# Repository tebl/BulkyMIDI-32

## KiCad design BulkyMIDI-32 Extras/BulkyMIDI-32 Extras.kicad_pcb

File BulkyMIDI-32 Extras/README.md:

# BulkyMIDI-32 Extras
Building the BulkyMIDI-32, I quickly ran into a bit of a problem with the format I had decided upon - I simply desired too many features to be able to fit all of it onto a $5 PCB (100x100mm). The solution came to me, weak and weary in a midnight dreary. Pondering over a quaint volume of forgotten TTL-lore, suddenly a raven came to be sitting upon my chamber door shouting: 

> Take all of the functionality that can be considered *"extra"* somewhere else. This way noone will have to build all of it in order to enjoy having an MT32-PI. 

You don't mess around with ravens, so I did as was told. This is why the project now has an *extras*-board. Build what you need, if you must. It's not like this story was true - except for the part where I ran out of board space.

The additional features provided by this module are as follows:
* RS-232 circuitry for communicating with a PC, this allows the installed Arduino Pro Micro to perform baud rate translation when communicating with MIDI-equipment through a PCs serial port. This is needed because MIDI uses a custom baud rate, generally well outside the tolerances of what a regular serial card can communicate at.
* Passive two-channel audio mixer, allowing you to mix the soundeffects coming from the sound card with that of the MIDI module without dealing with configuring a mixer in software on the card.
* Status LEDs
* Three extra MIDI ports that can individually be configured to serve as additional OUT or THRU ports.

For the most part you would only install the components for the features that you need or want, the links below will allow you to jump to a specific point in the build process and to access other details. Do however start at the beginning, but do not be alarmed at the sheer length of the build process - most of it'll take a lot longer to describe than it is to simply implement them.

- [1> Building the device](#1-building-the-device)
  - [1.1> Soldering it together](#11-soldering-it-together)
  - [1.2> Install LEDs](#12-install-leds)
  - [1.3> Electrolytics](#13-electrolytics)
  - [1.4> Connectors](#14-connectors)
  - [1.5> Installing the firmware](#15-installing-the-firmware)
  - [1.6> Finishing touches](#16-finishing-touches)
- [2> Schematic](#2-schematic)
- [3> BOM](#3-bom)

# 1> Building the device
Building a device such as this assumes you have at least minor experience soldering things together, recommended is that you at the very least have access to a soldering station with adjustable temperature. If currently available, you should probably start with 60/40 rosin core solder as the lead-free alternatives tends to be a bit harder to work with.

With the equipment sorted, now comes the shopping - so head on over to the [BOM](#3-bom)-section for some information on what kind of components that you'll need. Note that with sites such as ebay, AliExpress and similar sites that sell cheap chinese components, you'll need to treat these as a suggested search term and look for something that matches the gallery pictures.

Given the features listed at the start of this document, there are quite possibly a few of those you won't need or want as they can be considered separate from the main device though they will for the most part be related to the rabbit-hole I fell into when first starting out constructing the BulkyMIDI-32. There may certainly be some overlap between them, but it is a starting point (U1 will be needed for both MCU and the main device ports). The colours are as follows:

* **Green** components are used when we want the device to perform baud rate translation, this is used when receiving data via either the RS232-module or MIDI IN that is sent in a different baud rate from what a real MIDI-module expects. The closest baud rate on a PC would be 38400, well outside the tolerance of MIDI devices expecting 31250 baud.
* **Gray** components are only needed when using the *extras* board by itself, this is only relevant for the baud rate translation features described above.
* Components marked in **purple** indicate components directly adding features to the main BulkyMIDI-32 module. These include the addition of a rotary encoder module, additional *MIDI OUT* ports as well as *MIDI THRU* ports.
* **Yellow** components are for the RS-232, the Arduino Pro Micro takes care of handling the baud rate translation between RS-232 and the MIDI ports. 
* Finally, the **blue** components implement a simple passive audio mixer. It supports two channels when the *extras* board is used a standalone module, when connecting to it to the main module the audio output from that is used a third channel.

The build instructions from this point on will aim for the installation of most of the features, but feel free to leave out functionality you don't need according to colour chart above.

**NB!** Don't worry if the sheer length of this document looks intimidating, it's just a running commentary on everything that is done and updated pictures as we go along in the build process. Everything will be explained in due time, quite possibly including a lot more information than what would normally be needed for anyone with passable familiarity with soldering things together.

## 1.1> Soldering it together
The construction of this unit should be fairly straight-forward, just take your time in order to make sure everything goes into place - more or less straight. I usually recommend starting by having a good look at the PCBs, then try to figure out where the components should go and in particular the orientation they should be installed - it may be a case of round thing going into another round thing, but this is electronics and the small details matter. As mentioned in the previous section, you may not want every feature so pay attention to the colour coding when deciding what to leave out.

**NB!** This is revision F of the board, the changes to the revision G is the addition of a couple of diodes. 

I will usually try to install components sorted by their physical size, doing it this way means you'll have an easier time keeping everything from looking somewhat crooked. This is your board, your build and you want it perfect - don't you? If you said no, then go sit in the corner because I worked hard on creating this for myself and whoever wants to build one.

Here we've started by soldering all of the resistors, ensuring that we're using the correct values in each position. A single glass 1n4148 diode has also been installed, pay particular attention so that the black band matches that of the markings on the PCB. As previously mentioned, revision G also includes a 1n4001 diode to be installed at D1 (to the right of the *BAUD RATE*-diagram) - this is a larger black diode with a silver band instead and should also be installed as indicated.

Given that space will inevitably get tight, I like to get the solder jumpers handled early - less chance of accidentally melting a socket or two.
- You **need** to make a choice for **JP1-JP3**, regardless of whether you'll be installing the additional MIDI-connectors to the board - soldered across pins *1-2* makes the connector a THRU port while *2-3* makes it an extra OUT port. The little triangle above one of the pads denotes the first pin.
- The same goes for the **NO_555** jumper, soldering pins *1-2* when you're installing all of the LED components including the *555* and so on. Solder across pins *2-3* when building a simpler version of the board.

Sockets should be installed for the three ICs needed for the complete unit - you could probably manage without them if you know that you'll only be using known good parts. However, they're cheap and you could probably afford to not be quite so *cheap* as to skip them! Match the indent on the socket with that on the PCB. I recommend tacking opposing corners into place, then reheat the pins and push the socket flush against the board before soldering the remaining pins.

We've also gone ahead and installed our non-polarized capacitors, for the most part these will simply be 100nF (component marked *104*) decoupling caps added to ensure that the ICs function as intended and no values will be printed for them on the PCB. One of them will however not be the same as the rest, it is a 10nF capacitor that can be found directly below the space marked *74HCT14* (the component itself will be marked with the code *103*).

A single transistor is also used, a 2n3906 in a TO-92 package. If you're lucky enough to find them at a reasonable price, you can get transistors with pre-bent legs to match the footprint directly - because I couldn't, I instead just bent them outwards myself. The reason for this is simply that I prefer soldering with a larger tip, so the use of a wider footprint makes it a lot easier to avoid accidentally shorting the legs together. Looking at one from the top, you'll notice that it has a flat and a curved side to them - this needs to be matched up to the footprint.

## 1.2> Install LEDs
Somehow I managed the rather impressive task of coming up with a rather strange way of mounting the LEDs, requiring me to write a separate chapter on the things. Anyway, the idea was to have the LEDs facing forwards with the leads having been bent so that the rear of the LED sit flush against the edge of the PCB.

Each of the pins on the LED have their own names, it's actually just a diode that happens to light up when energized. I can never remember which of them is which, so for ease of reference I'll just say that you need to ensure that the longer pin goes into the round pad. If you look closely at the LED you'll see that the legs have a bit of a flattened bit to it, this is the part that needs to be in the PCB when bending then push the plastic of the housing flat against the PCB edge.

Solder in place once you are happy with the results. Personally I don't like the light bleed you get between the LEDs, generally they are so efficient that they'll appear to light up slightly just from the glow of the LED beside it. One way to reduce that is to slide a section on top of the LED so that only the front part of it is uncovered.

## 1.3> Electrolytics
With the LEDs in place, we've already moved on to other things. The electrolytic capacitors, or condensers if you're getting old like me. The one at *C6* ensures that everything on the board is properly powered. It's polarized component, meaning that we need to put it in the correct way or it won't work right. The stripe on its housing indicates the negative side, this matches up with the filled-in area of the footprint. As with the LEDs, the pins certainly have names that I'm incapable of remembering, so I'll just tell you to put the longer pin into the hole closest to the little plus sign (might need a magnifier to find it).

The same goes for *C8*, it is a smaller capacitor used for the timing on the 555. If you like to see the little LED flickering to show activity, just go ahead and install the 1uF component as indicated. If you would like it to stay on as long as there's data coming in at a regular pace, consider increasing the value to 3.3uF or even 4.7uF instead.

## 1.4> Connectors

Finally getting around to something intended for a bit of audio, the 3.5mm audio jacks. Given that the board incorporates a way of passively mixing up to two signals into the main audio coming from the MT32-PI, we probably should use differently coloured connectors to separate the output (green) from the inputs (black connectors). Technically the inputs should have been blue or quite possibly red, but I can't seem to find someone selling them, so I went with black instead. 

One step we need to pay particular attention to is how the *extras*-board would connect up with the main *BulkyMIDI-32*, specified as *J4* here. For my prototypes I've installed some extra long female pin headers as the one shown above on the main unit, only requiring standard male pin headers on this board. The spacing between these need to be correct, so I recommend that you try out the fit between the two modules with 20mm hex standoffs in between - **before** actually soldering anything in place.

If you've decided upon how to connect the *extras*-board to the main board, then we'll continue on with the installation - starting with making a few decisions on how to install the Arduino Pro Micro.

I need to say a few words about the various Arduino Pro Micro variants that are out there, one of the common variants encountered is more narrow than the others - to accommodate for this there is a duplicated row on one side. For reference I'm installing some female pin headers onto the Arduino itself, that way I can remove the board and use it for something else later. If you don't want to do all that you could just solder the two together, just make sure to install them according to the width of the board that you have.

The rest is to install the rest. Merely this and nothing more.

That includes a female right-angle DB9 connector, a barrel connector and at least the MIDI OUT on the top right of the board. If you want to use the audio mixer you'll need the potentiomenters as well.

The added MIDI ports on the right side of the module, labelled MIDI 1 through 3, can be set to either be used as *MIDI THRU* or *MIDI OUT*. From the best of my knowledge, the *THRU* variety is used by the MT32-PI to send a copy of all received MIDI messages to any connected devices. *OUT* on the other hand will be messages sent by MT32-PI, often a copy of the same messages though they may have had changes and filtering applied to them. *JP1* through *JP3* specifies the configuration for each connection, just pay attention that the order of them may not be as expected.

**NB!** If you have not already done as told, you need to solder each of these solder jumpers - even if you're skipping the installation of the connectors. When in doubt or for where you don't want to make an informed decision, just link pins 1-2 with the little triangle indicating pin 1.

## 1.5> Installing the firmware
This section will be a bit truncated, simply because the project includes different firmware that can be installed on the Arduino Pro Micro, each bringing different functionality into the mix. When in doubt the firmware you're looking for is probably the BaudRateConverter.

- [BaudRateConverter](https://github.com/tebl/BulkyMIDI-32/tree/main/software/arduino/BaudrateConverter) takes care of reading MIDI-data sent to it over RS-232, then retransmitting it over a standard 5-pin MIDI-cable. This is handy when using the device with an old laptop that may not have a MIDI-enabled gameport, but instead has a free serial port.
- [DebugMIDI](https://github.com/tebl/BulkyMIDI-32/tree/main/software/arduino/DebugMidi) gives you a simple debugging tool for MIDI-data, printing details for MIDI-messages received via a MIDI-cable. This is all handled via a command-line interface available via USB (running at 115200 baud).

Most of these will in some part need the [Arduino MIDI Library](https://github.com/FortySevenEffects/arduino_midi_library), the installation of which will be somewhat different depending on your choice of IDE for Arduino. PlatformIO, the one I'm using has the capability of installing the libraries for you automatically, but as as the Arduino IDE remains the most used I'll cover the process going forward.

Installing additional libraries in the Arduino IDE is done from *Tools* -> *Manage libraries*, the resulting dialog allows you to search for them by name. Unfortunately the search function leaves quite a bit to be desired and there are quite a lot of them to choose from, so I recommend limiting by the topic *Communication* before attempting to browse the results. The one you're looking for is *MIDI Library* by Francois Best. Click install to have the software do its thing. 

The second issue is simply that the *Arduino Pro Micro* isn't actually an official board created by Arduino, it's a significantly smaller Chinese copy of the Arduino Leonardo. What that means for us is that it doesn't have a suitable board definition for this board out of the box. This is easily fixed, going from *Tools* -> *Board: ...* .> *Boards Manager ...* - the one to look for will be named *SparkFun AVR Boards*.

The next step is simply to select the board type as *SparkFun Pro Micro*, under *Processor* you need to ensure that *ATMega32U4 (5v, 16Mhz)* have been selected. Attempting to upload code to the board with the wrong setting here may cause problems communicating with it later, it's recoverrable - it's just an annoying process that involves shorting the reset pin at a specific point on startup.

With everything set up correctly, simply hit compile and upload to send it over to the Arduino Pro Micro. This should complete without any errors.

## 1.6> Finishing touches
With the firmware in place, there isn't much more that is left to do other than connect the two modules together using the 20mm standoffs in between the two, making sure that the central connector mates up correctly. Add the faceplate to the top, finally a front plate goes on the front of the device. If you have any knobs that will fit onto the knurled shafts of the potentiometers, those also go a long way towards a professional look. You may find that some of the rotary encoders come with a D-type shaft instead, but it may be worth ordering one with the same shaft as the potentiometers - makes it a lot easier to find matching knobs.

With all of that done, it's time to enjoy some game - or at the very least have it loop the games title music, just to listen to all the glory that is the Roland MT-32 (at least as close as we can get without buying one). 

# 2> Schematic
The supplied KiCad files should be sufficient as both a schematic and as a  starting point for ordering PCBs (basically you could just zip the contents of the export folder and upload that on a fabrication site), the schematic is also available in [PDF-format](https://github.com/tebl/BulkyMIDI-32/tree/main/documentation/schematic) and this is what you'll need to print and work your way through this things don't work as expected after assembly.

# 3> BOM
Most parts should be easy to get a hold of from your favourite local electronic component shop, but given that I don't have access to such shops where I live so everything was based on whatever I could get cheapest from eBay/AliExpress. You can often get free shipping, but plan on waiting 3-4 weeks for delivery so plan accordingly.

As detailed elsewhere in the [build](#1-building-the-device) portion of this document, you can simply choose to install the features you want in order to cut down on the construction costs or simply limit yourself to those that you have the parts for. To keep the BOM-portion below somewhat readable, the item counts in parenthesis are optional and consists mainly of parts related to the baud rate conversion feature as well as additional *MIDI OUT* and *MIDI THRU* ports. Note that some of the listings have been repeated as they are listed with different description, so order what you need and check the list twice.

| Reference               | Item                                                              | Count | Order  |
| ----------------------- | ----------------------------------------------------------------- | ----- | ------ |
| BulkyMIDI-32 Extras     | Fabricate using Gerber files                                      |     1 | [PCBWay](https://www.pcbway.com/project/shareproject/BulkyMIDI_32_Extras_9be44f98.html)
| A1                      | Arduino Pro Micro (5v 16Mhz)                                      |    (1)|
|                         | 12-pin straight pin header                                        |    (2)|
| C1,C10                  | 100nF ceramic capacitor (5mm)                                     |     2 |
| C2-C5,C11 *             | 100nF ceramic capacitor (5mm)                                     |     5 |
| C6                      | 470uF electrolytic capacitor (8mm x 3.5mm)                        |     1 |
| C8                      | 1uF electrolytic capacitor (5mm x 2mm)                            |     1 |
| C9                      | 10nF ceramic capacitor (5mm)                                      |     1 |
| D2,D4                   | 5mm LEDs, preferably frosted (not the bright clear ones)          |    (3)|
| D1,D5                   | 1N4001 diode DO-41                                                |     2 |
| D3 *                    | 1N4148N small signal diode (DO-35)                                |    (1)|
| J1                      | 2.1mm x 5.5mm barrel plug                                         |    (1)|
| J4                      | 10-pin dual row female pin header (extra long, see [documentation](#14-connectors)) |     1 |
| J2,J3,J5,J10,J11        | Female S-terminal 5pin DIN PCB                                    |    (5)|
| J6 *                    | Right-angle female DB9 connector (PCB mount)                      |    (1)|
| J7-J9                   | PJ-317 (5-pin 3.5mm audio jack), preferably 2x blue and 1x green  |     3 |
| J12 *                   | 6-pin segment of male pin headers, with pin 5 removed             |    (1)|
| J14 *                   | 2-pin segment of male pin headers                                 |    (1)|
| J13 *                   | 2x3 segment of dual row male pin headers                          |    (1)|
| J14 *                   | 2x2 segment of dual row male pin headers                          |    (1)|
| J16                     | RS-232-module stacked on top of J6, wired to pads below module    |    (1)|
| JP7                     | 2-pin segment of male pin headers                                 |     1 |
| Q1                      | 2n3906 transistor (TO-92)                                         |     1 |
| R1,R2,R18 *             | 220 ohm resistor                                                  |    (3)|
| R3,R6,R13,R14,R15,R16 * | 220 ohm resistor                                                  |    (6)|
| R5                      | 2k2 (2200) ohm resistor                                           |    (1)|
| R7-R12                  | 1k ohm resistor                                                   |     6 |
| R17 *                   | 10k ohm resistor                                                  |    (1)|
| R19                     | 2k2 (2200) ohm resistor                                           |     2 |
| R20 *                   | 2k2 (2200) ohm resistor                                           |    (1)|
| R21                     | 100k ohm resistor                                                 |     1 |
| R22                     | 10k ohm resistor                                                  |     1 |
| RV1,RV2                 | RV097G 10k (stereo audio potentimeter)                            |     2 |
| U1                      | 74HCT14 (DIP-14)                                                  |     1 |
| U2 **                   | MAX232A (DIP-16)                                                  |    (1)|
| U3 *                    | 6N138 opto-coupler (DIP-8)                                        |    (1)|
| U4                      | NE555P (DIP-8)                                                    |     1 |
| Mounting ****           | Nylon M3 hex standoffs 20mm (M-F)                                 |     4 |
| Mounting ****           | Nylon M3x6mm nylon nuts                                           |     6 |

*) These components are only needed when installing the MCU for baud rate conversion.

**) Note the specification of a MAX232**A**, the older MAX232 without the *A* won't function without changes to the circuit. The same goes for Chinese clones, often sold as MAX232CPE. When in doubt, pick these up from a reputable electronics vendor.

***) These are used to hold the RS-232-modules in place, especially if you plan on installing two of them. With only the one module you can use shorter screws instead.

****) These are used in various places of the project, these are available in the form of kits usually advertised *M3 nylon standoff kit* which should contain most of what you'd need.

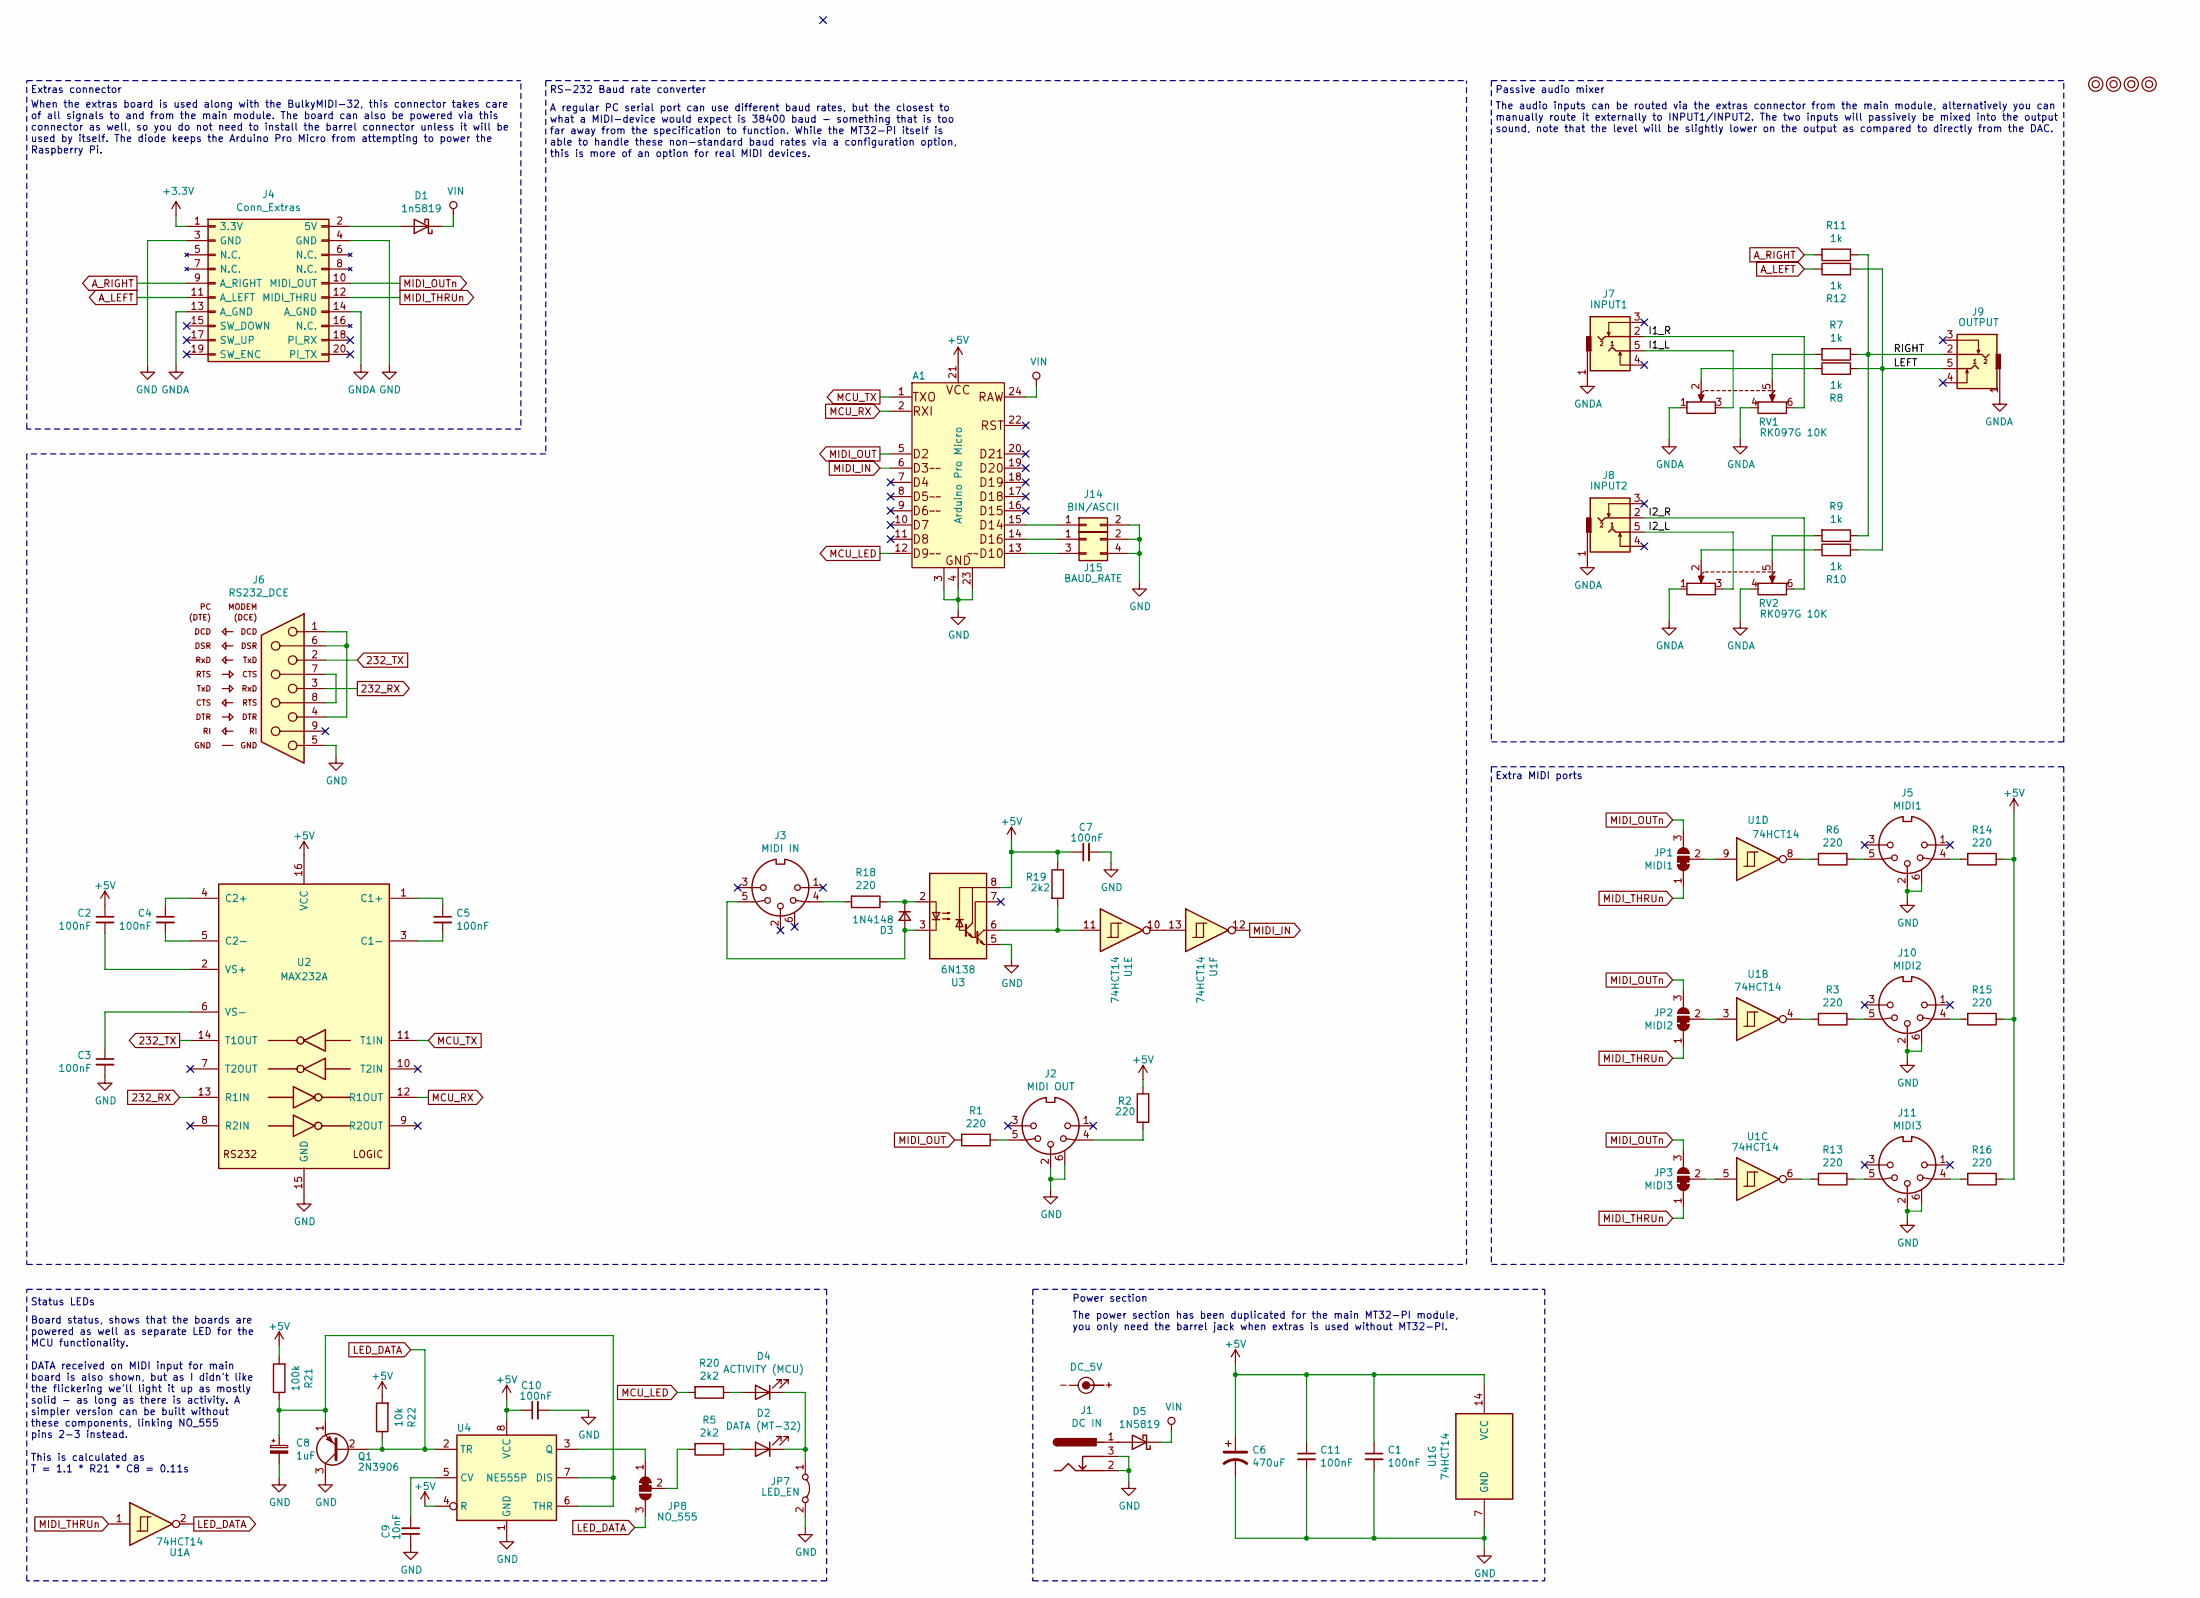
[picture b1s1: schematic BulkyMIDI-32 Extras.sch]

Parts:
A1: Arduino Pro Micro; Arduino_Pro_Micro
C1, C2, C3, C4, C5, C7, C10, C11: 100nF; C_Disc_D4.7mm_W2.5mm_P5.00mm
C6: 470uF; CP_Radial_D8.0mm_P3.50mm
C8: 1uF; CP_Radial_D5.0mm_P2.00mm
C9: 10nF; C_Disc_D4.7mm_W2.5mm_P5.00mm
D1: 1n5819; D_DO-41_SOD81_P10.16mm_Horizontal
D2: DATA (MT-32); LED_D5.0mm_Horizontal_O1.27mm_Z3.0mm
D3: 1N4148; D_DO-35_SOD27_P7.62mm_Horizontal
D4: ACTIVITY (MCU); LED_D5.0mm_Horizontal_O1.27mm_Z3.0mm
D5: 1N5819; D_DO-41_SOD81_P10.16mm_Horizontal
J1: DC IN; BARREL_JACK
J2: MIDI OUT; DIN5_MIDI_OUT
J3: MIDI IN; DIN5_MIDI_IN
J4: Conn_Extras; PinHeader_2x10_P2.54mm_Vertical
J5: MIDI1; DIN5_MIDI_OUT
J6: RS232_DCE; DSUB-9_Female_Horizontal_P2.77x2.84mm_EdgePinOffset7.70mm_H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
J7: INPUT1; PJ-317_IN
J8: INPUT2; PJ-317_IN
J9: OUTPUT; PJ-317_OUT
J10: MIDI2; DIN5_MIDI_OUT
J11: MIDI3; DIN5_MIDI_OUT
J14: BIN/ASCII; PinHeader_1x02_P2.54mm_Vertical
J15: BAUD_RATE; PinHeader_2x02_P2.54mm_Vertical
JP1: MIDI1; SolderJumper-3_P1.3mm_Open_Pad1.0x1.5mm
JP2: MIDI2; SolderJumper-3_P1.3mm_Open_Pad1.0x1.5mm
JP3: MIDI3; SolderJumper-3_P1.3mm_Open_Pad1.0x1.5mm
JP7: LED_EN; PinHeader_1x02_P2.54mm_Vertical
JP8: NO_555; SolderJumper-3_P1.3mm_Open_Pad1.0x1.5mm
M1, M2, M3, M4: Mounting; M3
Q1: 2N3906; TO-92_Inline_Wide
R1, R2, R3, R6, R13, R14, R15, R16, R18: 220; R_Axial_DIN0207_L6.3mm_D2.5mm_P10.16mm_Horizontal
R5, R19, R20: 2k2; R_Axial_DIN0207_L6.3mm_D2.5mm_P10.16mm_Horizontal
R7, R8, R9, R10, R11, R12: 1k; R_Axial_DIN0207_L6.3mm_D2.5mm_P10.16mm_Horizontal
R21: 100k; R_Axial_DIN0207_L6.3mm_D2.5mm_P10.16mm_Horizontal
R22: 10k; R_Axial_DIN0207_L6.3mm_D2.5mm_P10.16mm_Horizontal
RV1, RV2: RK097G 10K; RK097G
SYM1: DC_5V; PWR_Specification
U1: 74HCT14; DIP-14_W7.62mm_Socket_LongPads
U2: MAX232A; DIP-16_W7.62mm_Socket_LongPads
U3: 6N138; DIP-8_W7.62mm_Socket_LongPads
U4: NE555P; DIP-8_W7.62mm_Socket_LongPads

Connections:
232_RX: J6.3, U2.13 (R1IN)
232_TX: J6.2, U2.14 (T1OUT)
+5V: A1.21 (VCC), C1.1, C2.1, C6.1, C7.1, C10.1, C11.1, R2.1, R14.1, R15.1, R16.1, R19.1, R21.2, R22.2, U1.14 (VCC), U2.16 (VCC), U3.8 (VCC), U4.4 (R), U4.8 (VCC)
/I1_L: J7.5, RV1.3
/I1_R: J7.2, RV1.6
/I2_L: J8.5, RV2.3
/I2_R: J8.2, RV2.6
/LEFT: J9.5, R8.2, R10.2, R12.2
/RIGHT: J9.2, R7.1, R9.1, R11.1
A_LEFT: J4.11 (A_LEFT), R12.1
A_RIGHT: J4.9 (A_RIGHT), R11.2
GND: A1.3 (GND), A1.4 (GND), A1.23 (GND), C1.2, C3.2, C6.2, C7.2, C8.2, C9.1, C10.2, C11.2, J1.2, J1.3, J2.2, J2.6, J4.3 (GND), J4.4 (GND), J5.2, J5.6, J6.5, J10.2, J10.6, J11.2, J11.6, J14.2, J15.2, J15.4, JP7.2 (B), Q1.3 (C), U1.7 (GND), U2.15 (GND), U3.5 (GND), U4.1 (GND)
GNDA: J4.13 (A_GND), J4.14 (A_GND), J7.1, J8.1, J9.1, RV1.1, RV1.4, RV2.1, RV2.4
LED_DATA: JP8.3 (B), Q1.2 (B), R22.1, U1.2, U4.2 (TR)
MCU_LED: A1.12 (D9), R20.2
MCU_RX: A1.2 (RXI), U2.12 (R1OUT)
MCU_TX: A1.1 (TXO), U2.11 (T1IN)
MIDI_IN: A1.6 (D3), U1.12
MIDI_OUT: A1.5 (D2), R1.2
MIDI_OUTn: J4.10 (MIDI_OUT), JP1.3 (B), JP2.3 (B), JP3.3 (B)
MIDI_THRUn: J4.12 (MIDI_THRU), JP1.1 (A), JP2.1 (A), JP3.1 (A), U1.1
unnamed: A1.13 (D10), J15.3
unnamed: A1.14 (D16), J15.1
unnamed: A1.15 (D14), J14.1
unnamed: C2.2, U2.2 (VS+)
unnamed: C3.1, U2.6 (VS-)
unnamed: C4.1, U2.4 (C2+)
unnamed: C4.2, U2.5 (C2-)
unnamed: C5.1, U2.1 (C1+)
unnamed: C5.2, U2.3 (C1-)
unnamed: C8.1, Q1.1 (E), R21.1, U4.6 (THR), U4.7 (DIS)
unnamed: C9.2, U4.5 (CV)
unnamed: D1.2 (A), J4.2 (5V)
unnamed: D2.1 (K), D4.1 (K), JP7.1 (A)
unnamed: D2.2 (A), R5.1
unnamed: D3.1 (K), R18.1, U3.2 (C1)
unnamed: D3.2 (A), J3.5, U3.3 (C2)
unnamed: D4.2 (A), R20.1
unnamed: D5.2 (A), J1.1
unnamed: J2.4, R2.2
unnamed: J2.5, R1.1
unnamed: J3.4, R18.2
unnamed: J5.4, R14.2
unnamed: J5.5, R6.1
unnamed: J6.1, J6.4, J6.6
unnamed: J6.7, J6.8
unnamed: J10.4, R15.2
unnamed: J10.5, R3.1
unnamed: J11.4, R16.2
unnamed: J11.5, R13.1
unnamed: JP1.2 (C), U1.9
unnamed: JP2.2 (C), U1.3
unnamed: JP3.2 (C), U1.5
unnamed: JP8.1 (A), U4.3 (Q)
unnamed: JP8.2 (C), R5.2
unnamed: R3.2, U1.4
unnamed: R6.2, U1.8
unnamed: R7.2, RV1.5
unnamed: R8.1, RV1.2
unnamed: R9.2, RV2.5
unnamed: R10.1, RV2.2
unnamed: R13.2, U1.6
unnamed: R19.2, U1.11, U3.6 (VO2)
unnamed: U1.10, U1.13
VIN: A1.24 (RAW), D1.1 (K), D5.1 (K)

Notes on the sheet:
RS-232 Baud rate converter
Power section
Passive audio mixer
Extras connector
When the extras board is used along with the BulkyMIDI-32, this connector takes care of all signals to and from the main module. The board can also be powered via this connector as well, so you do not need to install the barrel connector unless it will be used by itself. The diode keeps the Arduino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
The audio inputs can be routed via the extras connector from the main module, alternatively you can manually route it externally to INPUT1/INPUT2. The two inputs will passively be mixed into the output sound, note that the level will be slightly lower on the output as compared to directly from the 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
Status LEDs
Extra MIDI ports
Board status, shows that the boards are powered as well as separate LED for the MCU functionality. DATA received on MIDI input for main board is also shown, but as I didn't like the flickering we'll light it up as mostly solid - as long as there is activity. A simpler version can be built without t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
The power section has been duplicated for the main MT32-PI module, you only need the barrel jack when extras is used without MT32-PI.
A regular PC serial port can use different baud rates, but the closest to what a MIDI-device would expect is 38400 baud - something that is too far away from the specification to function. While the MT32-PI itself is able to handle these non-standard baud rates via a configuration option, this is m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

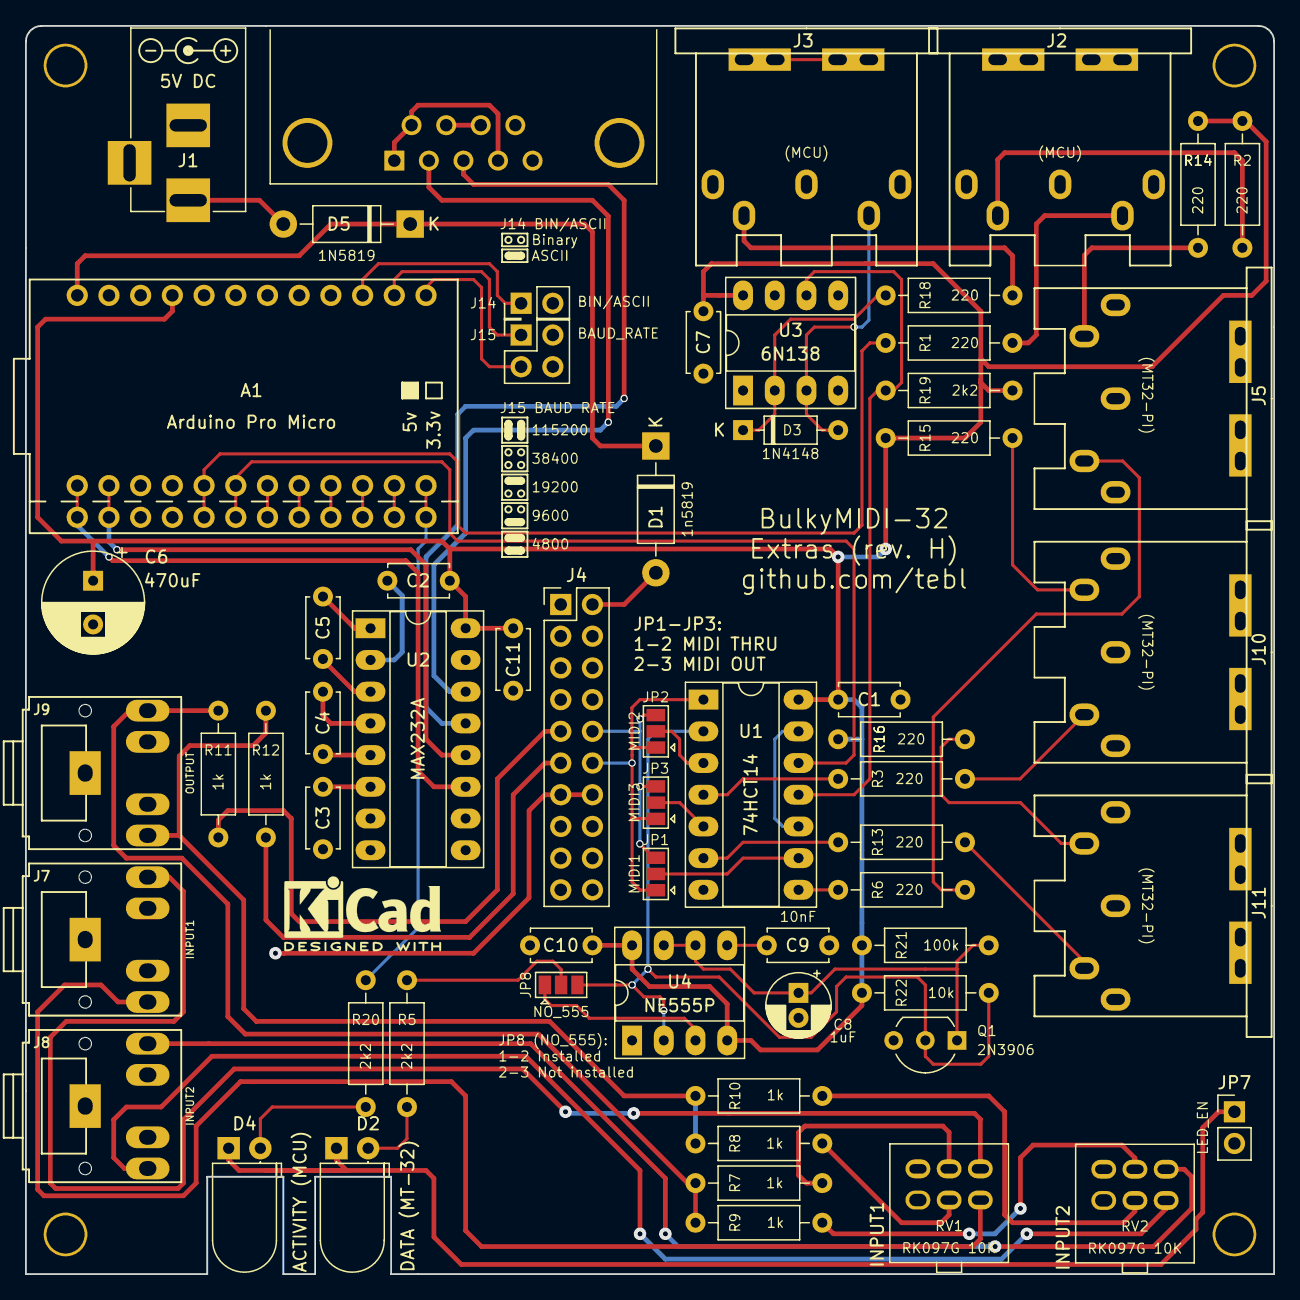
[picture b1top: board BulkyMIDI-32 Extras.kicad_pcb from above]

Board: 2 copper layers, 100.0 x 100.0 mm, 67 parts (0 on the bottom side), 65 nets.

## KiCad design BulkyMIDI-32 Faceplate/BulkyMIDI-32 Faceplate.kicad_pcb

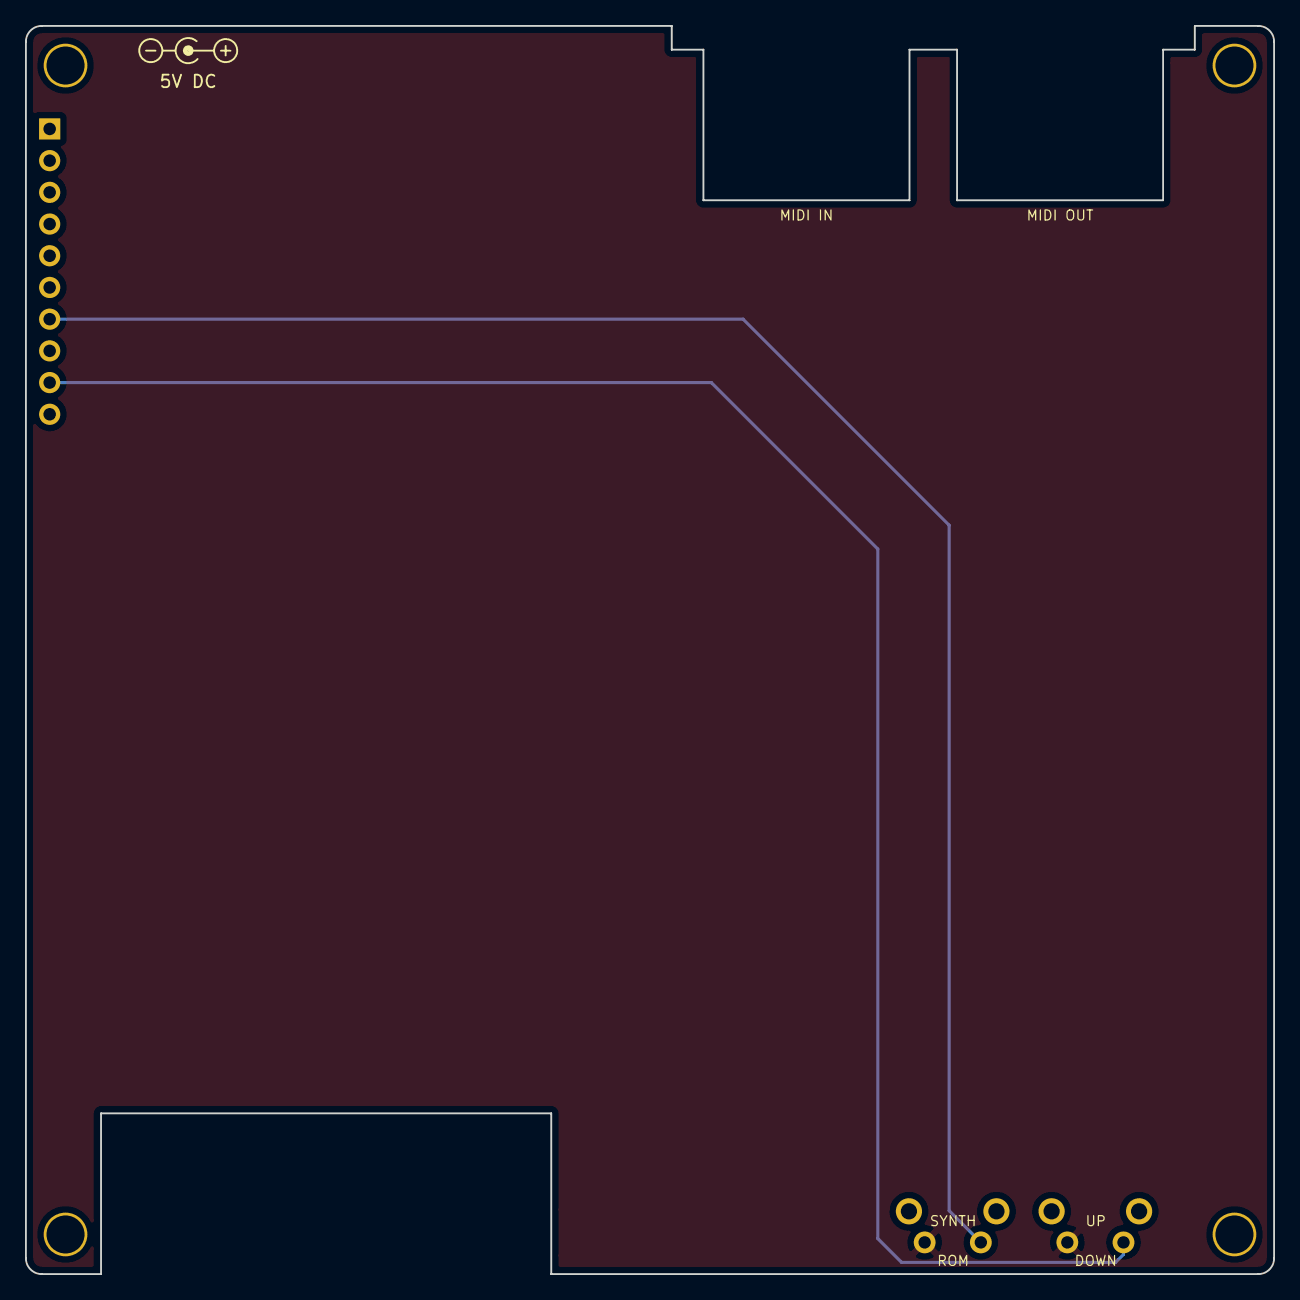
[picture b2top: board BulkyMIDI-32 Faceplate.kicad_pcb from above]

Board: 2 copper layers, 100.0 x 100.0 mm, 7 parts (1 on the bottom side), 3 nets.

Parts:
J4: Faceplate; PinHeader_1x10_P2.54mm_Vertical
M1, M2, M3, M4: Mounting; M3
SW1: SYNTH; SW_Tactile_SPST_Angled_PTS645Vx39-2LFS_Underside
SW4: VOL_UP; SW_Tactile_SPST_Angled_PTS645Vx39-2LFS_Underside

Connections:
GND: SW1.1, SW4.1
SW_SYNTH: J4.7, SW1.2
SW_UP: J4.9, SW4.2

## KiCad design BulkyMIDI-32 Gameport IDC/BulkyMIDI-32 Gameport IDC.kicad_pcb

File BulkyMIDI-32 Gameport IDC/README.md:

# BulkyMIDI-32 Gameport (IDC)
This is an alternative version of [BulkyMIDI-32 Gameport](https://github.com/tebl/BulkyMIDI-32/tree/main/BulkyMIDI-32%20Gameport), the difference is that instead of a right-angle DB15 connector we've got an IDC connector. For more general information about what this adapter is and what it is, check out the documentation for the regular version.

Using a cable increases the cost of the unit slightly, as we'd need to buy the cable including any connectors not already on it (I've seen Uxcell-branded cables that are ready made on AliExpress and Ebay). Having the adapter on a cable means we've got the flexibility of using it mostly everywhere, primarily by not getting in the way of other inputs on the motherboard or sound card. The pinout should also match the same [pinout](https://www.frontx.com/cpx091_2.html) used on motherboard breakout cables (usually with pin 16 missing), so in theory you could use a 2x8 pin ribbon cable and connect it directly to a motherboard with internal gameport connector.

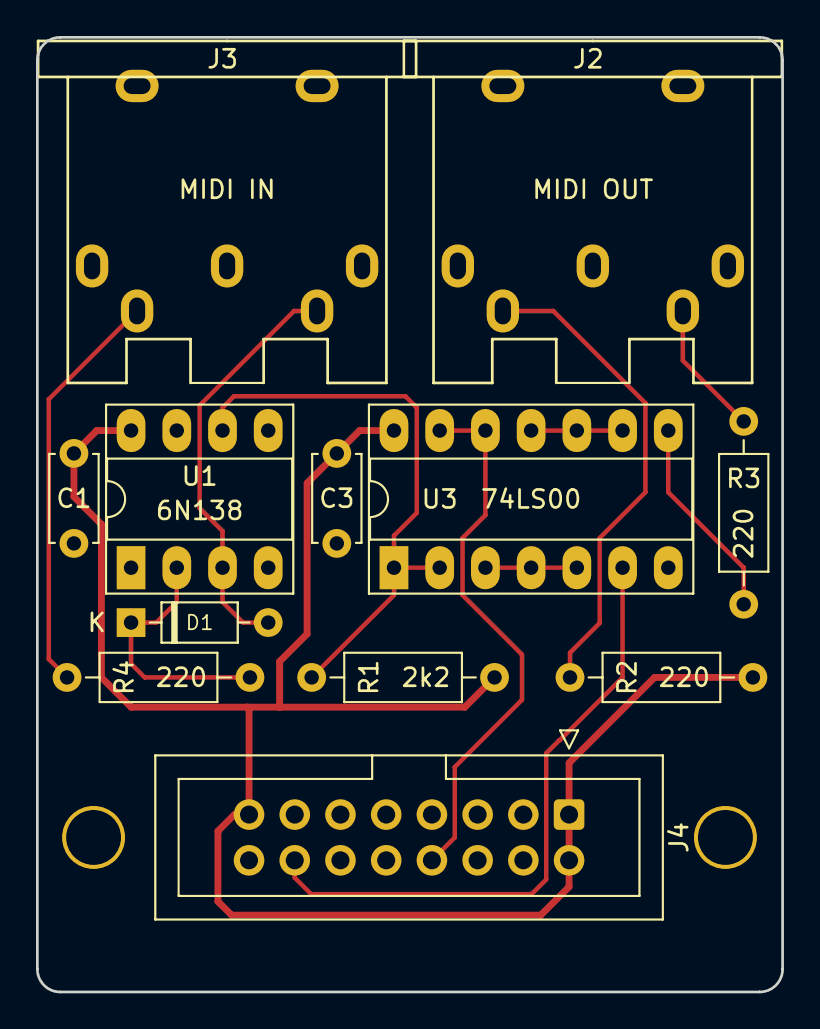
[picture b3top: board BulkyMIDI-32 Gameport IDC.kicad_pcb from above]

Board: 2 copper layers, 41.4 x 53.0 mm, 14 parts (0 on the bottom side), 13 nets.

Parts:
C1, C3: 100nF; C_Disc_D4.7mm_W2.5mm_P5.00mm
D1: 1N4148; D_DO-35_SOD27_P7.62mm_Horizontal
J2: MIDI OUT; DIN5_MIDI
J3: MIDI IN; DIN5_MIDI
J4: Gameport; Gameport_IDC
M1, M2: Mounting; M3
R1: 2k2; R_Axial_DIN0207_L6.3mm_D2.5mm_P10.16mm_Horizontal
R2, R3, R4: 220; R_Axial_DIN0207_L6.3mm_D2.5mm_P10.16mm_Horizontal
U1: 6N138; DIP-8_W7.62mm_Socket_LongPads
U3: 74LS00; DIP-14_W7.62mm_Socket_LongPads

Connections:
+5V: C1.1, C3.1, J4.1, J4.8, J4.9, R1.1, R2.1, U1.8, U3.14
GND: C1.2, C3.2, J2.2, J4.4, J4.5, U1.5, U3.7
MIDI_RxD: J4.15, U3.6
MIDI_TxD: J4.12, U3.12, U3.13
unnamed: D1.1, R4.1, U1.2
unnamed: D1.2, J3.5, U1.3
unnamed: J2.4, R2.2
unnamed: J2.5, R3.1
unnamed: J3.4, R4.2
unnamed: R1.2, U1.6, U3.1, U3.2
unnamed: R3.2, U3.8
unnamed: U3.3, U3.4, U3.5
unnamed: U3.9, U3.10, U3.11

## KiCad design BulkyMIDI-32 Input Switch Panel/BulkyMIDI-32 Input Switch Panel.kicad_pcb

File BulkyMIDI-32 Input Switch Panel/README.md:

# BulkyMIDI-32 Input Switch Panel
This is a front-facing panel for controlling the *BulkyMIDI-32 Input Switch*, while optional by design I find that it makes the system a lot more enjoyable - both when in use, and living in a pile on my desk. The main PCB didn't have suffiecient room for the LEDs either, so if you'd like a little feedback on the currently active input channel then this is where you'd mount those without getting overly creative.

- [1> Building the device](#1-building-the-device)
  - [1.1> Soldering it together](#11-soldering-it-together)
- [2> Schematic](#2-schematic)
- [3> BOM](#3-bom)

# 1> Building the device
Building a device such as this assumes you have at least minor experience soldering things together, recommended is that you at the very least have access to a soldering station with adjustable temperature. If currently available, you should probably start with 60/40 rosin core solder as the lead-free alternatives tends to be a bit harder to work with.

With requirements for basic equipment sorted, we need to talk a bit about what you want to achieve while building this project. The reason I ask is that while you can build a functional [BulkyMIDI-32 Input Switch](https://github.com/tebl/BulkyMIDI-32/tree/main/BulkyMIDI-32%20Input%20Switch) using that module alone, you can also build the complete version of it - this includes including front panels (this module), as well as a set of two faceplates.

Now that you know what you want to build, we can get started on the most expensive step in any build process - shopping! So, head on over to the [BOM](#3-bom)-section for some information on what kind of components that you'll need. While I would have liked to give you specific part numbers for "reputable" electronic part suppliers, I can't afford to shop there so I usually make due with what I can find on sites such as ebay, AliExpress and any similar sites that sell cheap chinese components. The downside to this is that I can't link to a part directly and expect it to stay listed, so you'll need to consider the description listed as suggested search terms.

## 1.1> Soldering it together

The construction of this unit should be fairly straight-forward, just take your time in order to make sure everything goes into place - more or less straight. I usually recommend starting by having a good look at the PCBs, try to figure out where all of the listed components go and in which orientation they go in (all of this should be clearly marked on the silkscreen). 

The first component to be added is the right-angle pin headers, these are soldered on the front side of the board instead of the component side. I've found that these are often somewhat warped, so I usually try to just solder the outer edges first, then reheat and adjust so that the plastic part sits completely flush against the board before tackling the remaining pins.

The next component to go on are the 8mm hex standoffs, they in particular need to be positioned so that a flat edge lines up with the lef and right edges of the PCB. As these are just nylon, I've made things slightly easier for myself by using a sharp knife to trim a bit off the vertical edges of them - in particular the one that sits just above the power LED.

Here I've simply inserted the LEDs into the footprints (longer pin goes into the round pad), the same goes for the six switches before adding the front panel to the front of it.  Continuing on with the LEDs I'll tack one of the pins into place, then while reheating the pin I'll try and push slightly on it to ensure that it is perfectly aligned with the holes on the front panel before soldering the remaining pin. The switches mostly stick to their expected alignment, but feel free to use the same method except that you push from the from.

The front panel have been removed again, mostly because it'll slightly be in the way when installing it onto the main [BulkyMIDI-32 Input Switch](https://github.com/tebl/BulkyMIDI-32/tree/main/BulkyMIDI-32%20Input%20Switch) PCB. If you're a perfectionist like me, you may want to deal with some of the light bleed that you'll inevitably get between the LEDs.

The easiest solution for this came to me in the middle of a dark and stormy night, standard heat shrink tubing with a diameter of at least 5mm. Using an 8mm hex standoff as a guide and a sharp knife, I cut it into 8mm segments that was then just put on top of the LEDs. If you have a hot air station you can shrink it a bit to keep it from falling off when the front panel is removed, but as long as it stays in place they should as well. 

# 2> Schematic
The supplied KiCad files should be sufficient as both a schematic and as a  starting point for ordering PCBs (basically you could just zip the contents of the export folder and upload that on a fabrication site), the schematic is also available in [PDF-format](https://github.com/tebl/BulkyMIDI-32/tree/main/documentation/schematic) and this is what you'll need to print and work your way through this things don't work as expected after assembly.

# 3> BOM
Most parts should be easy to get a hold of from your favourite local electronic component shop, but given that I don't have access to such shops where I live so everything was based on whatever I could get cheapest from eBay/AliExpress (free shipping, but plan on waiting 3-4 weeks for delivery). Components in parenthesis can be considered optional for features beyond the more basic functionality, but where's the fun in that? You deserve the complete package.

| Reference             | Item                                                              | Count | Order  |
| --------------------- | ----------------------------------------------------------------- | ----- | ------ |
| Panel PCB             | Fabricate using Gerber files                                      |     1 | PCBWay
| D1-D4,D7              | 5mm LEDs, preferably frosted (not the bright clear ones)          |     5 |
| J1                    | Breakable right-angle pin header                                  |     1 |
| SW1-SW4               | 6x6x11mm momentary button                                         |     6 |
| Mounting ****         | Nylon M3 hex standoffs 8mm (M-F)                                  |     4 |
| Mounting ****         | Nylon M3x6mm nylon screws                                         |     4 |
| Mounting ****         | Nylon M3x6mm nylon nuts                                           |     4 |

****) These are available in the form of kits usually advertised *M3 nylon standoff kit* which should contain most of what you'd need. I do however recommend that you pick up extra M-F standoffs of lengths 8mm and 20mm, as quite a lot of them will be used when building more than one module.

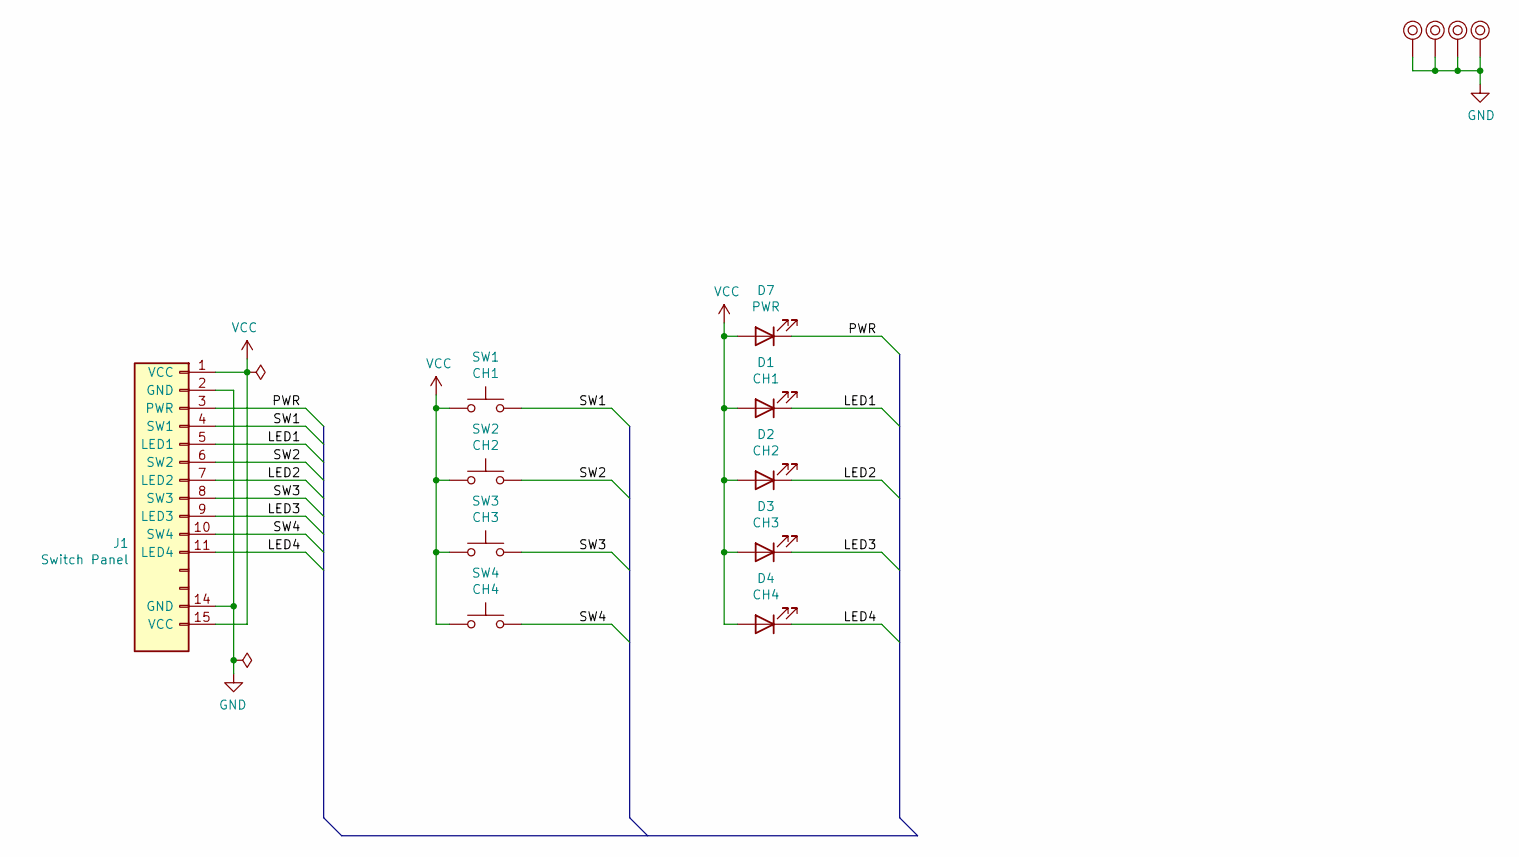
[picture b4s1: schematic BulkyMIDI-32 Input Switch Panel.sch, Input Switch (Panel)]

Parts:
D1: CH1; LED_D5.0mm
D2: CH2; LED_D5.0mm
D3: CH3; LED_D5.0mm
D4: CH4; LED_D5.0mm
D7: PWR; LED_D5.0mm
J1: Switch Panel; PinHeader_1x15_P2.54mm_Horizontal
M1, M2, M3, M4: Mounting_Pin; M3_pin
SW1: CH1; SW_PUSH_6mm
SW2: CH2; SW_PUSH_6mm
SW3: CH3; SW_PUSH_6mm
SW4: CH4; SW_PUSH_6mm

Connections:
/LED1: D1.1 (K), J1.5 (LED1)
/LED2: D2.1 (K), J1.7 (LED2)
/LED3: D3.1 (K), J1.9 (LED3)
/LED4: D4.1 (K), J1.11 (LED4)
/PWR: D7.1 (K), J1.3 (PWR)
/SW1: J1.4 (SW1), SW1.2
/SW2: J1.6 (SW2), SW2.2
/SW3: J1.8 (SW3), SW3.2
/SW4: J1.10 (SW4), SW4.2
GND: J1.2 (GND), J1.14 (GND), M1.1, M2.1, M3.1, M4.1
VCC: D1.2 (A), D2.2 (A), D3.2 (A), D4.2 (A), D7.2 (A), J1.1 (VCC), J1.15 (VCC), SW1.1, SW2.1, SW3.1, SW4.1

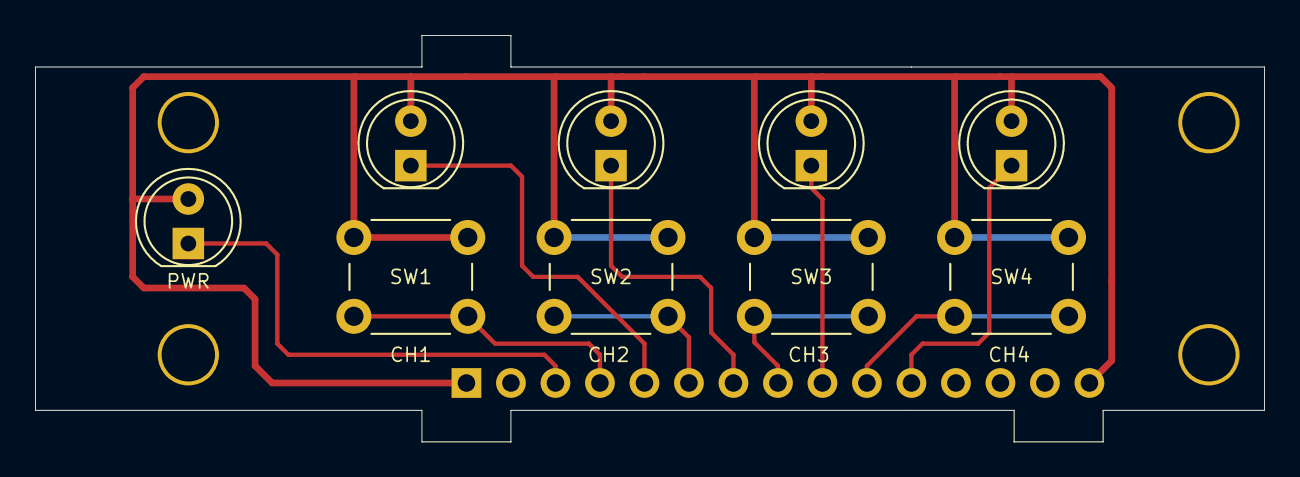
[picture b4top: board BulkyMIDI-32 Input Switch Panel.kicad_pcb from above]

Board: 2 copper layers, 70.2 x 23.2 mm, 14 parts (1 on the bottom side), 11 nets.
